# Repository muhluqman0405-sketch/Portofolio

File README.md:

# Muhammad Luqman — Engineering Portfolio

A Next.js App Router portfolio for electrical engineering projects, with a
small content layer that can be edited without changing the page components.

## Run locally

```bash
npm install
npm run dev
```

Open `http://localhost:3000` in a browser. Run `npm run check` for the
TypeScript and production-build checks.

## Edit the portfolio content

- Profile, education, focus areas, navigation, and contact links:
  `src/data/portfolio.ts`
- Project titles, summaries, tags, and artifact notes:
  `src/data/portfolio.ts`
- Instrumentation-amplifier layout image: `public/project-art/`

Project descriptions are limited to the supplied files and report material; no
performance claims are included.

## Production deployment

Run `npm ci` and `npm run check` before publishing. Vercel can detect this
Next.js project automatically; use the repository root and the default Next.js
build settings. The current site does not read environment variables.

Contact links are configured in `src/data/portfolio.ts`.

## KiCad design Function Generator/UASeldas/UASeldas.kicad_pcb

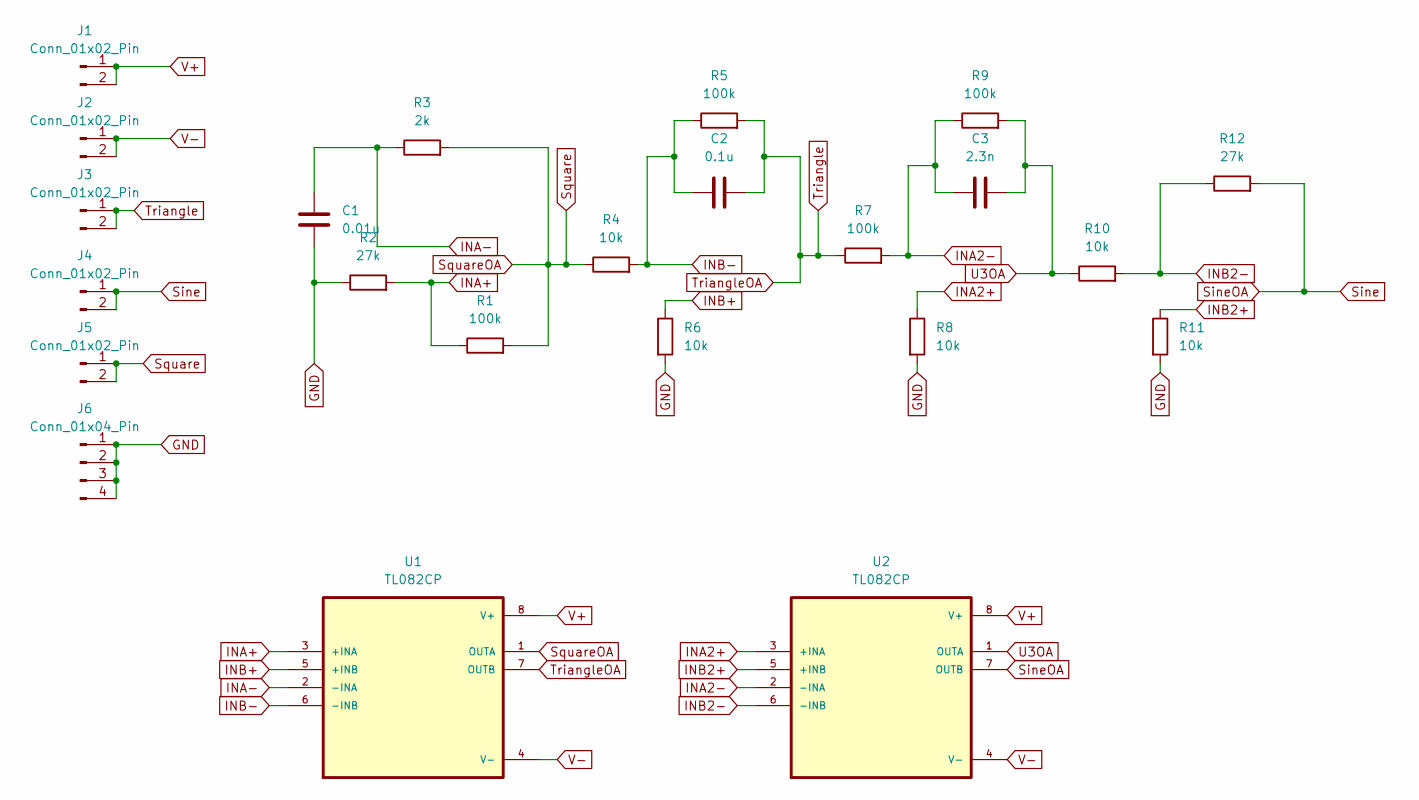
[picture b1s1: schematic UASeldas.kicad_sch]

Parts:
C1: 0.01u; CP_Radial_D8.0mm_P3.50mm
C2: 0.1u; CP_Radial_D8.0mm_P3.50mm
C3: 2.3n; CP_Radial_D8.0mm_P3.50mm
J1, J2, J3, J4, J5: Conn_01x02_Pin; PinHeader_1x02_P2.54mm_Vertical
J6: Conn_01x04_Pin; PinHeader_1x04_P2.54mm_Vertical
R1, R5, R7, R9: 100k; R_Axial_DIN0309_L9.0mm_D3.2mm_P15.24mm_Horizontal
R2, R12: 27k; R_Axial_DIN0309_L9.0mm_D3.2mm_P15.24mm_Horizontal
R3: 2k; R_Axial_DIN0309_L9.0mm_D3.2mm_P15.24mm_Horizontal
R4, R6, R8, R10, R11: 10k; R_Axial_DIN0309_L9.0mm_D3.2mm_P15.24mm_Horizontal
U1, U2: TL082CP; DIP794W45P254L959H508Q8

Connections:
GND: C1.2, J6.1, J6.2, J6.3, J6.4, R2.1, R6.2, R8.2, R11.2
INA2+: R8.1, U2.3 (+INA)
INA2-: C3.1, R7.2, R9.1, U2.2 (-INA)
INA+: R1.1, R2.2, U1.3 (+INA)
INA-: C1.1, R3.1, U1.2 (-INA)
INB2+: R11.1, U2.5 (+INB)
INB2-: R10.2, R12.1, U2.6 (-INB)
INB+: R6.1, U1.5 (+INB)
INB-: C2.1, R4.2, R5.1, U1.6 (-INB)
Sine: J4.1, J4.2, R12.2, U2.7 (OUTB)
Square: J5.1, J5.2, R1.2, R3.2, R4.1, U1.1 (OUTA)
Triangle: C2.2, J3.1, J3.2, R5.2, R7.1, U1.7 (OUTB)
U3OA: C3.2, R9.2, R10.1, U2.1 (OUTA)
V+: J1.1, J1.2, U1.8 (V+), U2.8 (V+)
V-: J2.1, J2.2, U1.4 (V-), U2.4 (V-)

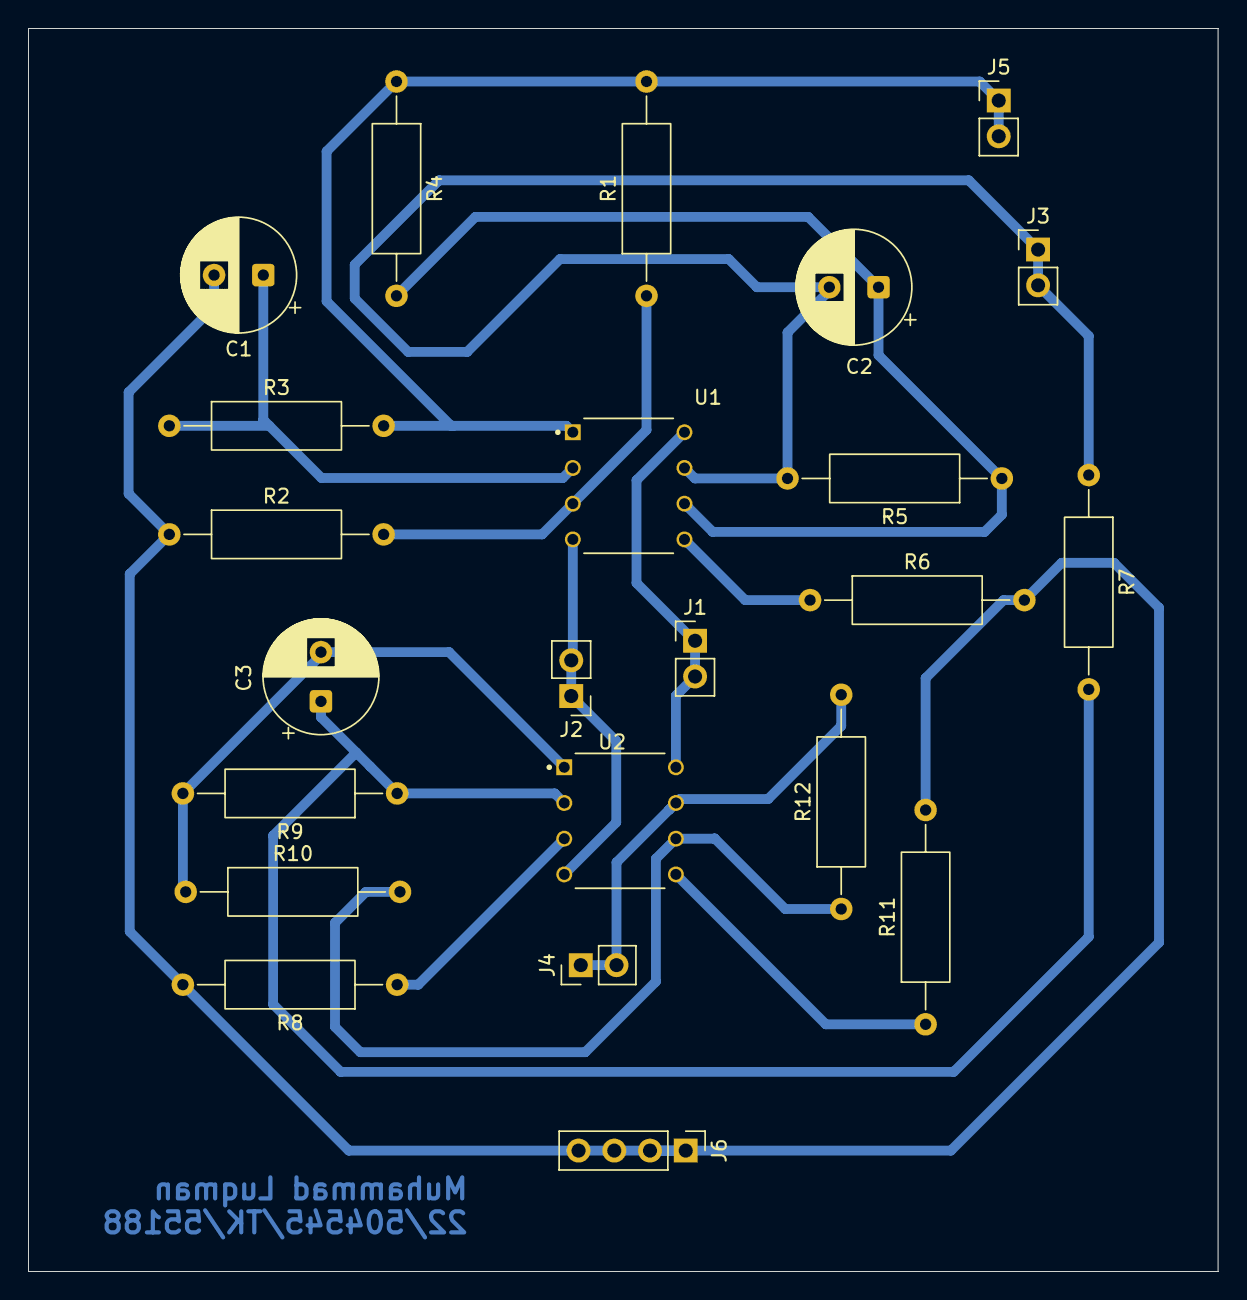
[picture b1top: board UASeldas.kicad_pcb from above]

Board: 2 copper layers, 84.6 x 88.4 mm, 23 parts (0 on the bottom side), 15 nets.
